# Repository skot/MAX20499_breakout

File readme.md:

### ** Maxim is not giving up the full datasheet for the MAX20499 without a NDA and "project approval" **
I'm abandoning this board.

## MAX20499C/D

- This design appears to work, in it's default output voltage (0.85V). I can't change it because I can't see the I2C register map without signing a NDA
- Sorta in stock DK and ME
- [Product Page](https://www.maximintegrated.com/en/products/power/switching-regulators/MAX20499C.html)
- Vin; 3-5.5V
- Vout; 0.5-1.275V
- Iout; 16/12A
- I2C adjustable output voltage in 6mV steps!
- [Devkit](https://www.maximintegrated.com/en/products/power/switching-regulators/MAX20499CEVKIT.html)

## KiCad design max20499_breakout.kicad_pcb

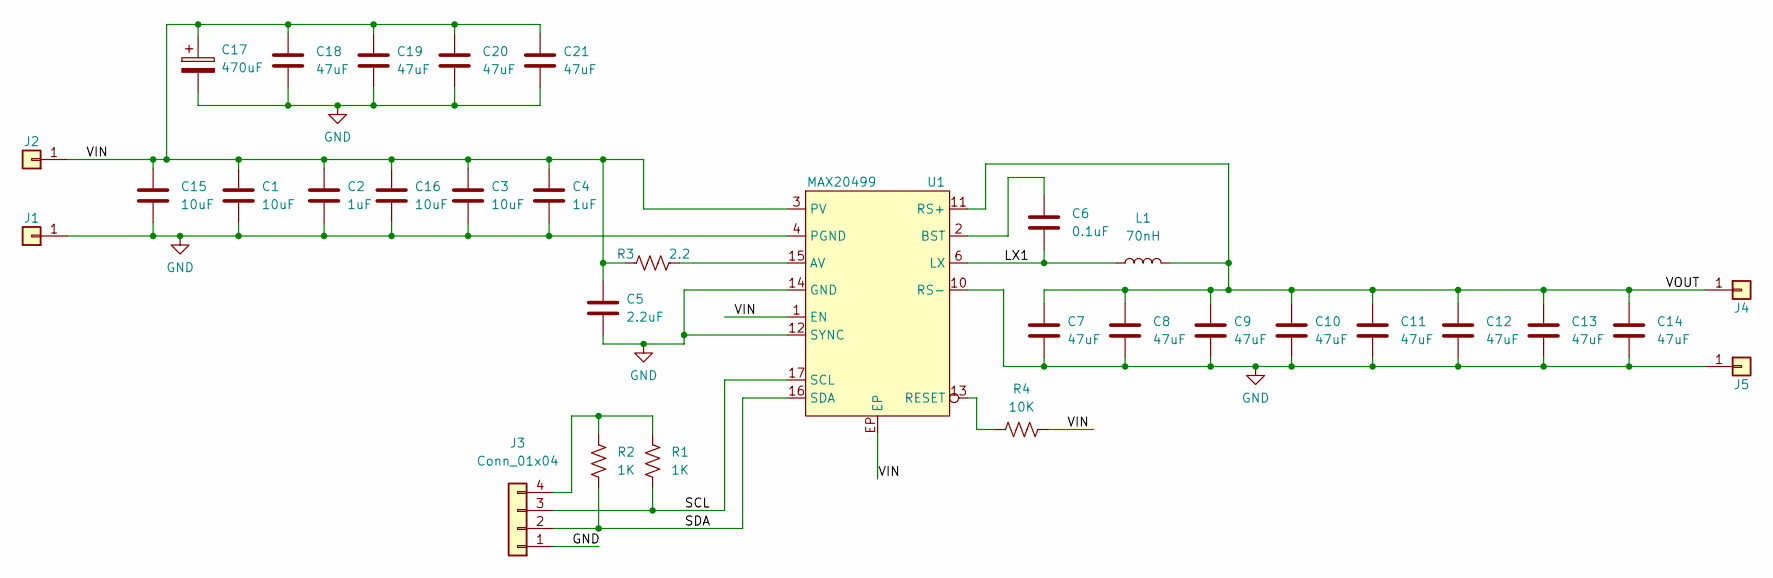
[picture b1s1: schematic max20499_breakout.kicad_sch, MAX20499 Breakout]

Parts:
C1, C3, C15, C16: 10uF; C_0805_2012Metric
C2, C4: 1uF; C_0603_1608Metric
C5: 2.2uF; C_0603_1608Metric
C6: 0.1uF; C_0603_1608Metric
C7, C8, C9, C10, C11, C12, C13, C14: 47uF; C_1206_3216Metric
C17: 470uF; CP_EIA-7343-43_Kemet-X
C18, C19, C20, C21: 47uF; C_1210_3225Metric
J1, J2, J4, J5: Conn_01x01; 63862-1
J3: Conn_01x04; PinHeader_1x04_P2.54mm_Vertical
L1: 70nH; VLBU9664100LT-R07M
R1, R2: 1K; R_0402_1005Metric
R3: 2.2; R_0402_1005Metric
R4: 10K; R_0402_1005Metric
U1: MAX20499; PARTNO MAX20499DAFOA/VY+

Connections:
/LX1: C6.2, L1.1, U1.6 (LX)
/SCL: J3.3, R1.2, U1.17 (SCL)
/SDA: J3.2, R2.2, U1.16 (SDA)
/VIN: C1.1, C2.1, C3.1, C4.1, C5.1, C15.1, C16.1, C17.1, C18.1, C19.1, C20.1, C21.1, J2.1, R3.1, R4.1, U1.1 (EN), U1.3 (PV), U1.9 (PV), U1.EP
/VOUT: C7.1, C8.1, C9.1, C10.1, C11.1, C12.1, C13.1, C14.1, J4.1, L1.2, U1.11 (RS+)
GND: C1.2, C2.2, C3.2, C4.2, C5.2, C7.2, C8.2, C9.2, C10.2, C11.2, C12.2, C13.2, C14.2, C15.2, C16.2, C17.2, C18.2, C19.2, C20.2, C21.2, J1.1, J3.1, J5.1, U1.4 (PGND), U1.5 (PGND), U1.7 (PGND), U1.8 (PGND), U1.10 (RS-), U1.12 (SYNC), U1.14 (GND)
unnamed: C6.1, U1.2 (BST)
unnamed: J3.4, R1.1, R2.1
unnamed: R3.2, U1.15 (AV)
unnamed: R4.2, U1.13 (RESET)

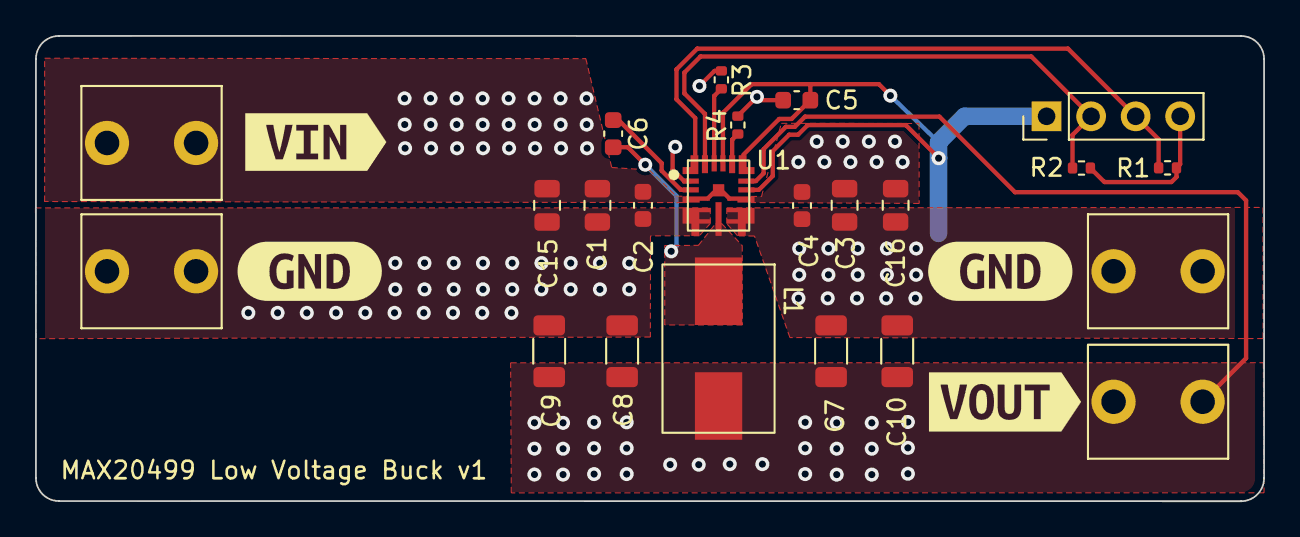
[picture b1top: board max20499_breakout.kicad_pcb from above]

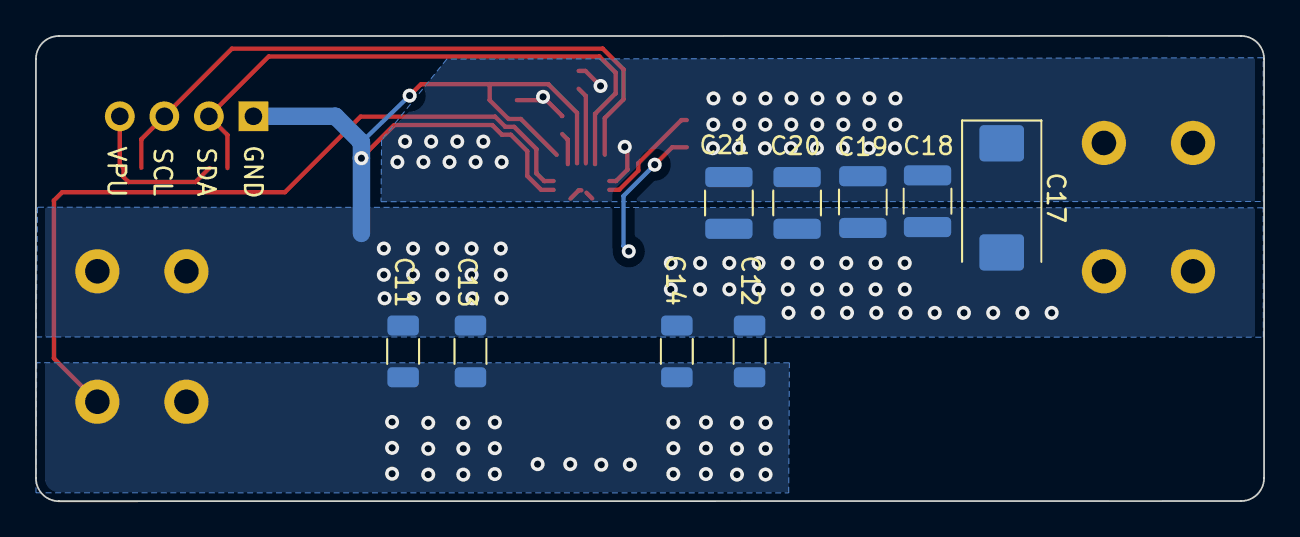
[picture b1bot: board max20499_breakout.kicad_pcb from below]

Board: 2 copper layers, 70.0 x 26.5 mm, 36 parts (9 on the bottom side), 10 nets.

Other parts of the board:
kibuzzard-62A80E9C: G***; kibuzzard-62A80E9C
kibuzzard-62A80EF8, kibuzzard-62A80EF8#2: G***; kibuzzard-62A80EF8
kibuzzard-62A80F52: G***; kibuzzard-62A80F52

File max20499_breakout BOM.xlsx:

Qty | Reference(s) | Value | DK
4 | C1, C3, C15, C16 | 10uF | 1276-6685-1-ND
2 | C2, C4 | 1uF | 1276-1942-1-ND
1 | C5 | 2.2uF | 1276-CL10Y225KP84PNCCT-ND
1 | C6 | 0.1uF | 1276-6717-1-ND
8 | C7, C8, C9, C10, C11, C12, C13, C14 | 47uF | 1276-1167-1-ND
1 | C17 | 470uF | 718-1749-1-ND
4 | C18, C19, C20, C21 | 47uF | 490-10531-1-ND
4 | J1, J2, J4, J5 | Conn_01x01 | A100886CT-ND
1 | J3 | Conn_01x04
1 | L1 | 70nH | 445-VLBU9664100LT-R07MCT-ND
2 | R1, R2 | 1K | 311-1.00KLRCT-ND
1 | R3 | 2.2000000000000002 | 311-2.20LRCT-ND
1 | R4 | 10K | RMCF0402FT10K0CT-ND
1 | U1 | MAX20499 | 175-MAX20499DAFOA/VY+-ND

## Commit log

2022-06-12 initial import
2022-06-12 added all of the passives to schematic
2022-06-13 finished schematic capture. started organizing PCB
2022-06-14 routed PCB
2022-06-14 added DK part numbers in schematic
2022-06-14 added readme and schematic PDF
2022-06-14 added manufacturing files, BOM and gerbers.
2022-06-14 lil' silkscreen tweak. regenerated gerbers
2022-06-14 new render
2022-06-14 ordered PCBs and Parts
2022-07-21 readme update after building boards
2022-07-22 abandon ship!
